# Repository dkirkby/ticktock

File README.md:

# Precision Pendulum Clock Metrology

This repository contains electronics schematics and a printed circuit board design for precision metrology of a pendulum clock.

The corresponding microcontroller firmware and unix server backend are hosted [here](https://github.com/captainkirkby/Gears).

For an overview of this project, see [this excerpt](https://github.com/dkirkby/ticktock/blob/master/InterfaceMagazineFall2015.pdf) from the Fall 2015 Issue of the [CalIT2](http://www.calit2.uci.edu) Interface Magazine.

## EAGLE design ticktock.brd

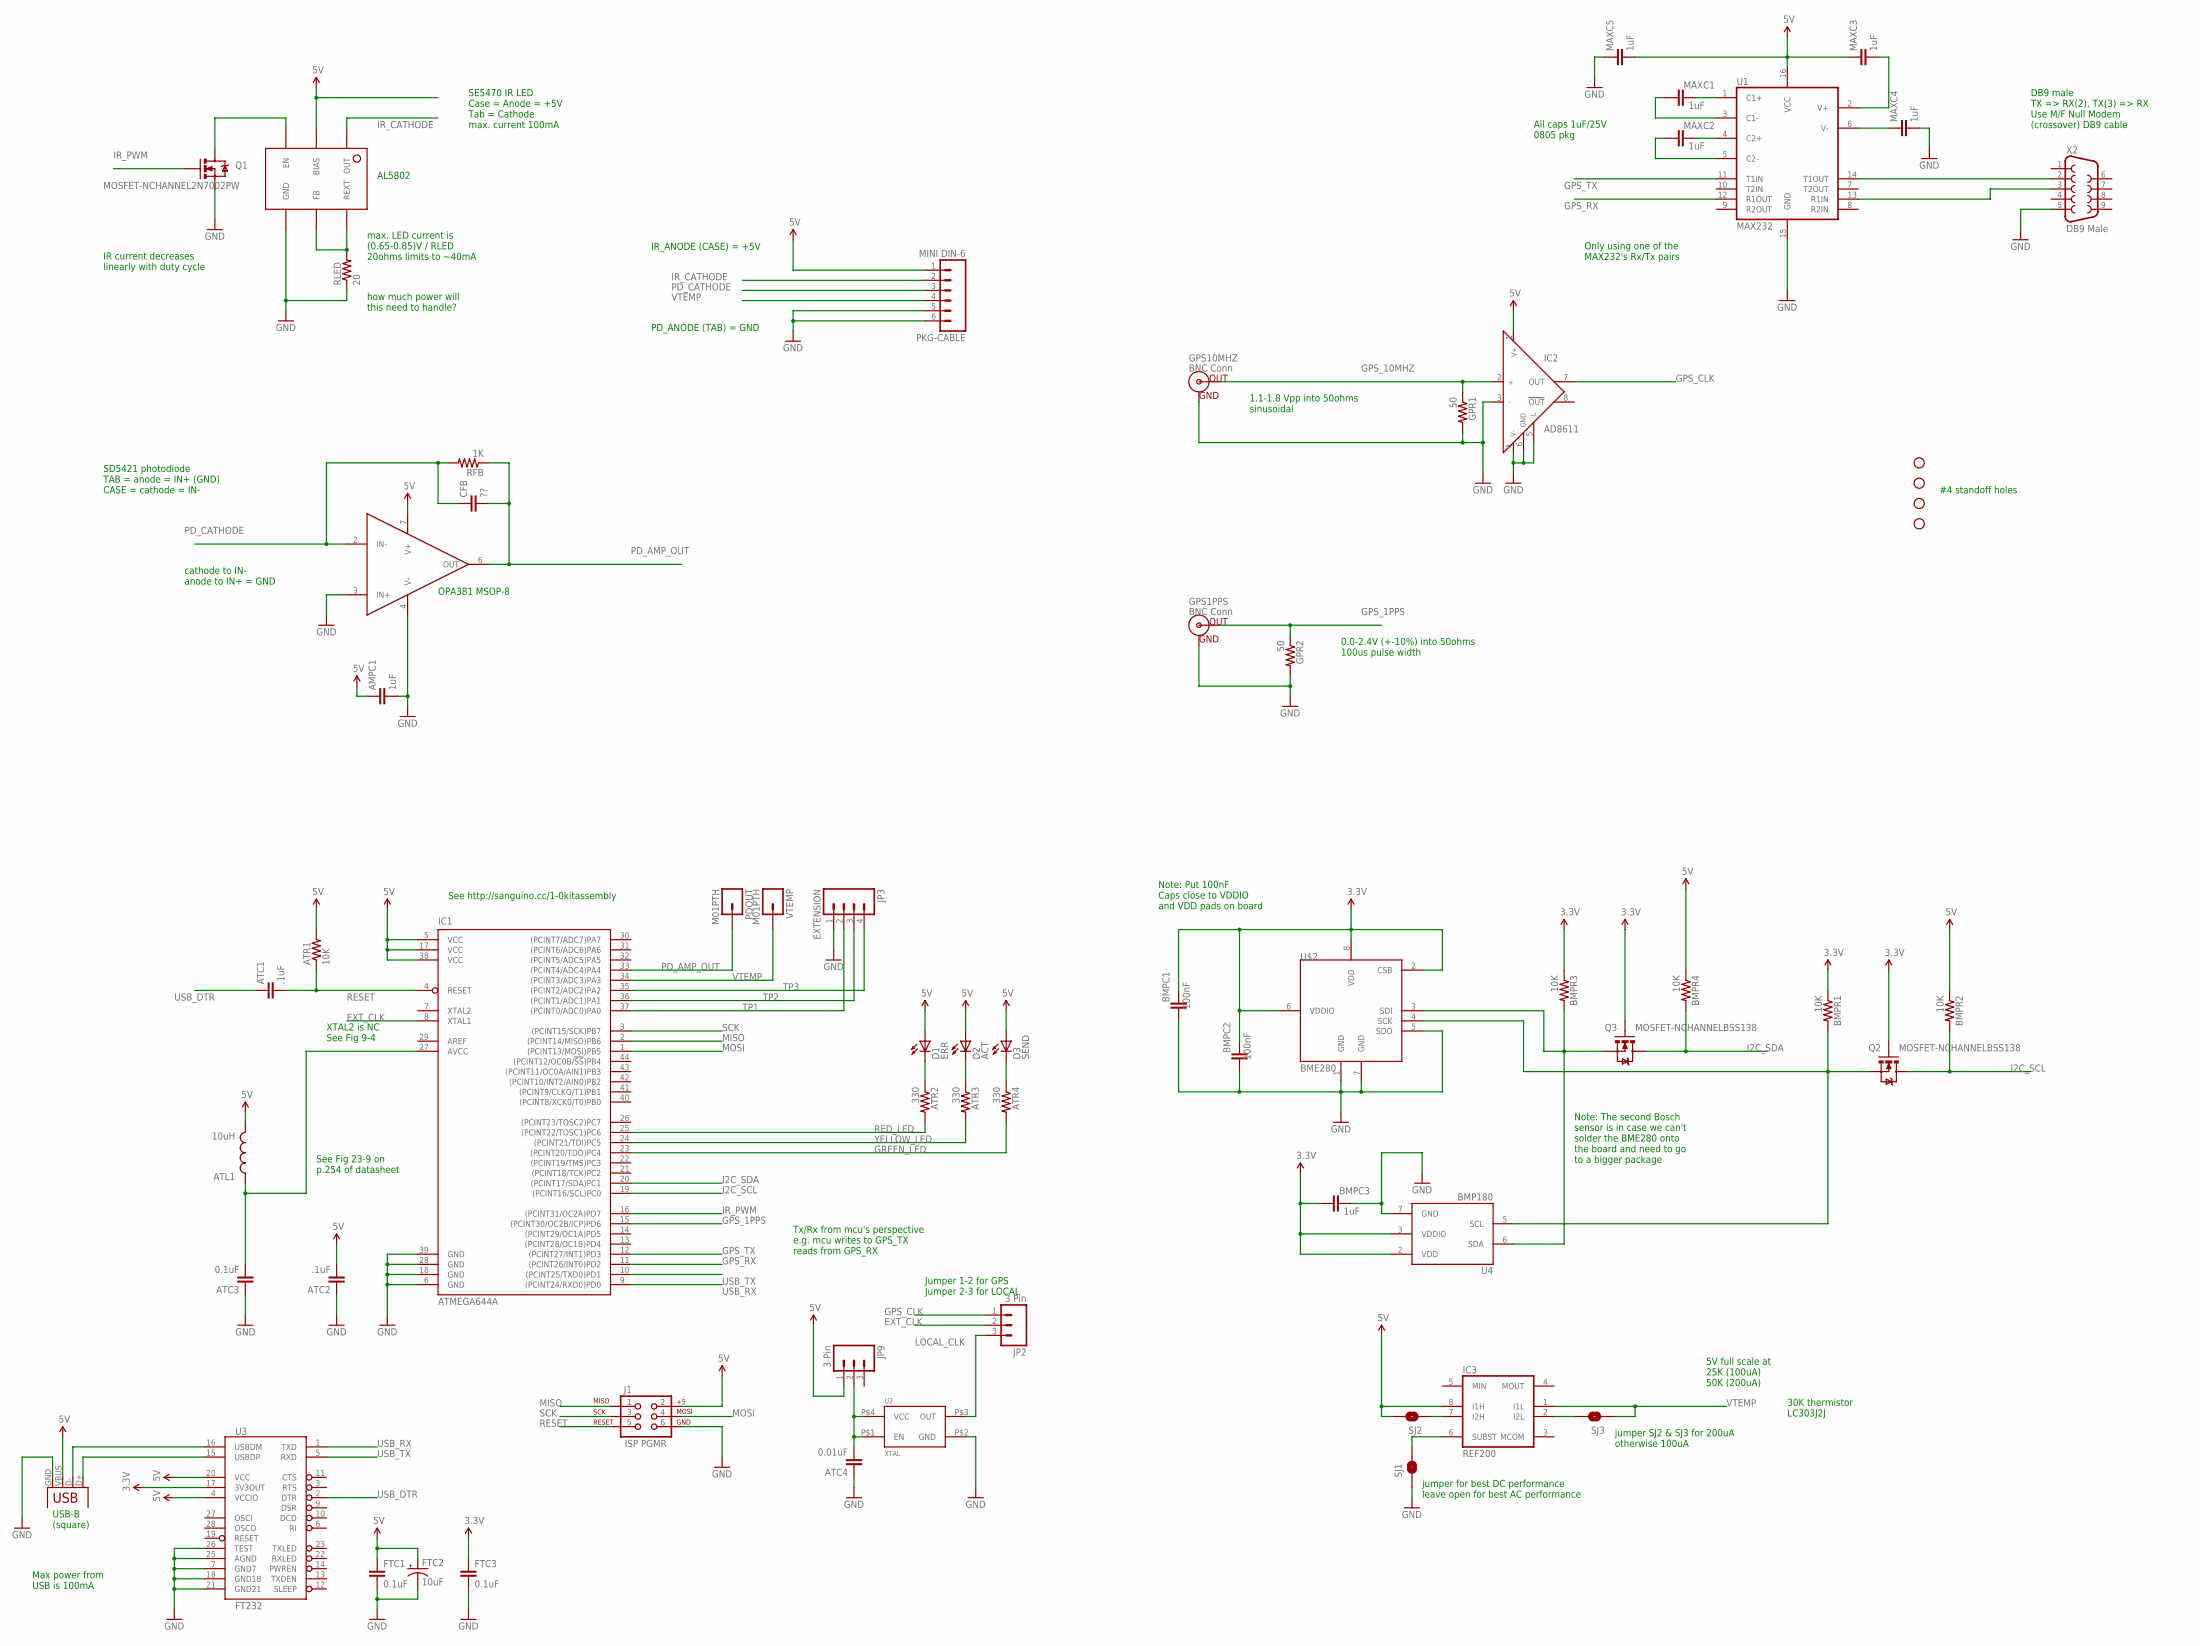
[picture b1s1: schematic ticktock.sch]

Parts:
AMPC1: 1uF; 0805
ATC1, ATC2: .1uF; 0805
ATC3: 0.1uF; 0805
ATC4: 0.01uF; 0805
ATL1: 10uH; 0805
ATR1: 10K; 0805
ATR2, ATR3, ATR4: 330; 0805
BMPC1, BMPC2: 100nF; 0805
BMPC3: 1uF; 0805
BMPR1, BMPR2, BMPR3, BMPR4: 10K; 0805
CFB: ??; 0805
D1: ERR; LED-1206
D2: ACT; LED-1206
D3: SEND; LED-1206
FTC1, FTC3: 0.1uF; 0805
FTC2: 10uF; EIA3216
GPR1, GPR2: 50; 0805
GPS1PPS, GPS10MHZ: BNC Conn; BNC
IC1: ATMEGA644A; TQFP44
IC2: AD8611; MSOP08
IC3: REF200; SO08
IC4: OPA381; MSOP08
IC5: AL5802
J1: ISP PGMR; 2X3-NS
JP1: Square USB; USB-B-PTH
JP2: 3 Pin; 1X03_LOCK
JP3: EXTENSION; 1X04_LOCK
JP9: 3-Pin; 1X03_LOCK
MAXC1, MAXC2, MAXC3, MAXC4, MAXC5: 1uF; 0805
PDOUT: M01PTH; 1X01
PKG-CABLE: MINI DIN-6; MINI-DIN6
Q1: MOSFET-NCHANNEL2N7002PW; SOT323
Q2, Q3: MOSFET-NCHANNELBSS138; SOT23
RFB: 1K; 0805
RLED: 20; 0805
SJ1, SJ2, SJ3: SOLDERJUMPERNO; SJ_2S-NO
STANDOFF1, STANDOFF2, STANDOFF3, STANDOFF4: STAND-OFF
U1: MAX232; SO016
U2: XTAL; CRYSTAL-SMD-7X5
U3: FT232; SSOP28DB
U4: BMP180
U$2: BME280
VTEMP: M01PTH; 1X01
X2: DB9 Male; DB9_MALE

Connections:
3.3V: BMPC1.2, BMPC2.2, BMPC3.1, BMPR1.1, BMPR3.1, FTC3.1, Q2.1 (G), Q3.1 (G), U3.17 (3V3OUT), U4.2 (VDD), U4.3 (VDDIO), U$2.2 (CSB), U$2.6 (VDDIO), U$2.8 (VDD)
5V: AMPC1.1, ATC2.2, ATL1.2, ATR1.2, BMPR2.1, BMPR4.1, D1.A, D2.A, D3.A, FTC1.1, FTC2.A (+), IC1.5 (VCC), IC1.17 (VCC), IC1.38 (VCC), IC2.1 (V+), IC3.8 (I1H), IC4.7 (V+), IC5.BIAS, J1.2, JP1.VBUS, JP9.1, MAXC3.1, MAXC5.2, PKG-CABLE.1, SJ2.2, U1.16 (VCC), U3.4 (VCCIO), U3.20 (VCC)
EXT_CLK: IC1.8 (XTAL1), JP2.2
GND: AMPC1.2, ATC2.1, ATC3.1, ATC4.1, BMPC1.1, BMPC2.1, BMPC3.2, FTC1.2, FTC2.C (-), FTC3.2, GPR1.2, GPR2.2, GPS1PPS.GND, GPS10MHZ.GND, IC1.6 (GND), IC1.18 (GND), IC1.28 (GND), IC1.39 (GND), IC2.3 (IN-), IC2.4 (V-), IC2.5 (L), IC2.6 (GND), IC4.3 (IN+), IC4.4 (V-), IC5.GND, J1.6, JP1.GND, JP3.1, MAXC4.2, MAXC5.1, PKG-CABLE.5, PKG-CABLE.6, Q1.2 (S), RLED.1, SJ1.1, U1.15 (GND), U2.P$2 (GND), U3.7 (GND7), U3.18 (GND18), U3.21 (GND21), U3.25 (AGND), U3.26 (TEST), U4.7 (GND), U$2.1 (GND), U$2.5 (SDO), U$2.7 (GND), X2.5
GPS_1PPS: GPR2.1, GPS1PPS.S (OUT), IC1.15 ((PCINT30/OC2B/ICP)PD6)
GPS_10MHZ: GPR1.1, GPS10MHZ.S (OUT), IC2.2 (IN+)
GPS_CLK: IC2.7 (OUT), JP2.1
GPS_RX: IC1.11 ((PCINT26/INT0)PD2), U1.12 (R1OUT)
GPS_TX: IC1.12 ((PCINT27/INT1)PD3), U1.11 (T1IN)
GREEN_LED: ATR4.2, IC1.23 ((PCINT20/TDO)PC4)
I2C_SCL: BMPR2.2, IC1.19 ((PCINT16/SCL)PC0), Q2.3 (D)
I2C_SDA: BMPR4.2, IC1.20 ((PCINT17/SDA)PC1), Q3.3 (D)
IR_CATHODE: IC5.OUT, PKG-CABLE.2
IR_PWM: IC1.16 ((PCINT31/OC2A)PD7), Q1.1 (G)
LOCAL_CLK: JP2.3, U2.P$3 (OUT)
MISO: IC1.2 ((PCINT14/MISO)PB6), J1.1
MOSI: IC1.1 ((PCINT13/MOSI)PB5), J1.4
unnamed: IC5.EN, Q1.3 (D)
unnamed: IC5.FB, IC5.REXT, RLED.2
unnamed: MAXC1.2, U1.1 (C1+)
unnamed: MAXC1.1, U1.3 (C1-)
unnamed: MAXC2.2, U1.4 (C2+)
unnamed: MAXC2.1, U1.5 (C2-)
unnamed: MAXC3.2, U1.2 (V+)
unnamed: U1.14 (T1OUT), X2.2
unnamed: MAXC4.1, U1.6 (V-)
unnamed: U1.13 (R1IN), X2.3
unnamed: JP1.D-, U3.16 (USBDM)
unnamed: JP1.D+, U3.15 (USBDP)
unnamed: ATC3.2, ATL1.1, IC1.27 (AVCC)
unnamed: IC3.6 (SUBST), SJ1.2
unnamed: BMPR1.2, Q2.2 (S), U4.5 (SCL), U$2.4 (SCK)
unnamed: ATR4.1, D3.C
unnamed: IC3.7 (I2H), SJ2.1
unnamed: IC3.2 (I2L), SJ3.2
unnamed: ATR3.1, D2.C
unnamed: ATR2.1, D1.C
unnamed: ATC4.2, JP9.2, U2.P$1 (EN), U2.P$4 (VCC)
unnamed: BMPR3.2, Q3.2 (S), U4.6 (SDA), U$2.3 (SDI)
PD_AMP_OUT: CFB.2, IC1.33 ((PCINT4/ADC4)PA4), IC4.6 (OUT), PDOUT.1, RFB.1
PD_CATHODE: CFB.1, IC4.2 (IN-), PKG-CABLE.3, RFB.2
RED_LED: ATR2.2, IC1.25 ((PCINT22/TOSC1)PC6)
RESET: ATC1.2, ATR1.1, IC1.4 (RESET), J1.5
SCK: IC1.3 ((PCINT15/SCK)PB7), J1.3
TP1: IC1.37 ((PCINT0/ADC0)PA0), JP3.2
TP2: IC1.36 ((PCINT1/ADC1)PA1), JP3.3
TP3: IC1.35 ((PCINT2/ADC2)PA2), JP3.4
USB_DTR: ATC1.1, U3.2 (DTR)
USB_RX: IC1.9 ((PCINT24/RXD0)PD0), U3.1 (TXD)
USB_TX: IC1.10 ((PCINT25/TXD0)PD1), U3.5 (RXD)
VTEMP: IC1.34 ((PCINT3/ADC3)PA3), IC3.1 (I1L), PKG-CABLE.4, SJ3.1, VTEMP.1
YELLOW_LED: ATR3.2, IC1.24 ((PCINT21/TDI)PC5)

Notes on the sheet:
max. LED current is (0.65-0.85)V / RLED 20ohms limits to ~40mA
SE5470 IR LED Case = Anode = +5V Tab = Cathode max. current 100mA
how much power will this need to handle?
IR current decreases linearly with duty cycle
AL5802
All caps 1uF/25V 0805 pkg
Only using one of the MAX232's Rx/Tx pairs
DB9 male TX => RX(2), TX(3) => RX Use M/F Null Modem (crossover) DB9 cable
USB-B (square)
Max power from USB is 100mA
See Fig 23-9 on p.254 of datasheet
IR_ANODE (CASE) = +5V
XTAL2 is NC See Fig 9-4
See http://sanguino.cc/1-0kitassembly
Jumper 1-2 for GPS Jumper 2-3 for LOCAL
0.0-2.4V (+-10%) into 50ohms 100us pulse width
1.1-1.8 Vpp into 50ohms sinusoidal
OPA381 MSOP-8
cathode to IN- anode to IN+ = GND
SD5421 photodiode TAB = anode = IN+ (GND) CASE = cathode = IN-
PD_ANODE (TAB) = GND
jumper for best DC performance leave open for best AC performance
jumper SJ2 & SJ3 for 200uA otherwise 100uA
5V full scale at 25K (100uA) 50K (200uA)
30K thermistor LC303J2J
#4 standoff holes
Note: Put 100nF Caps close to VDDIO and VDD pads on board
Note: The second Bosch sensor is in case we can't solder the BME280 onto the board and need to go to a bigger package
Tx/Rx from mcu's perspective e.g. mcu writes to GPS_TX reads from GPS_RX

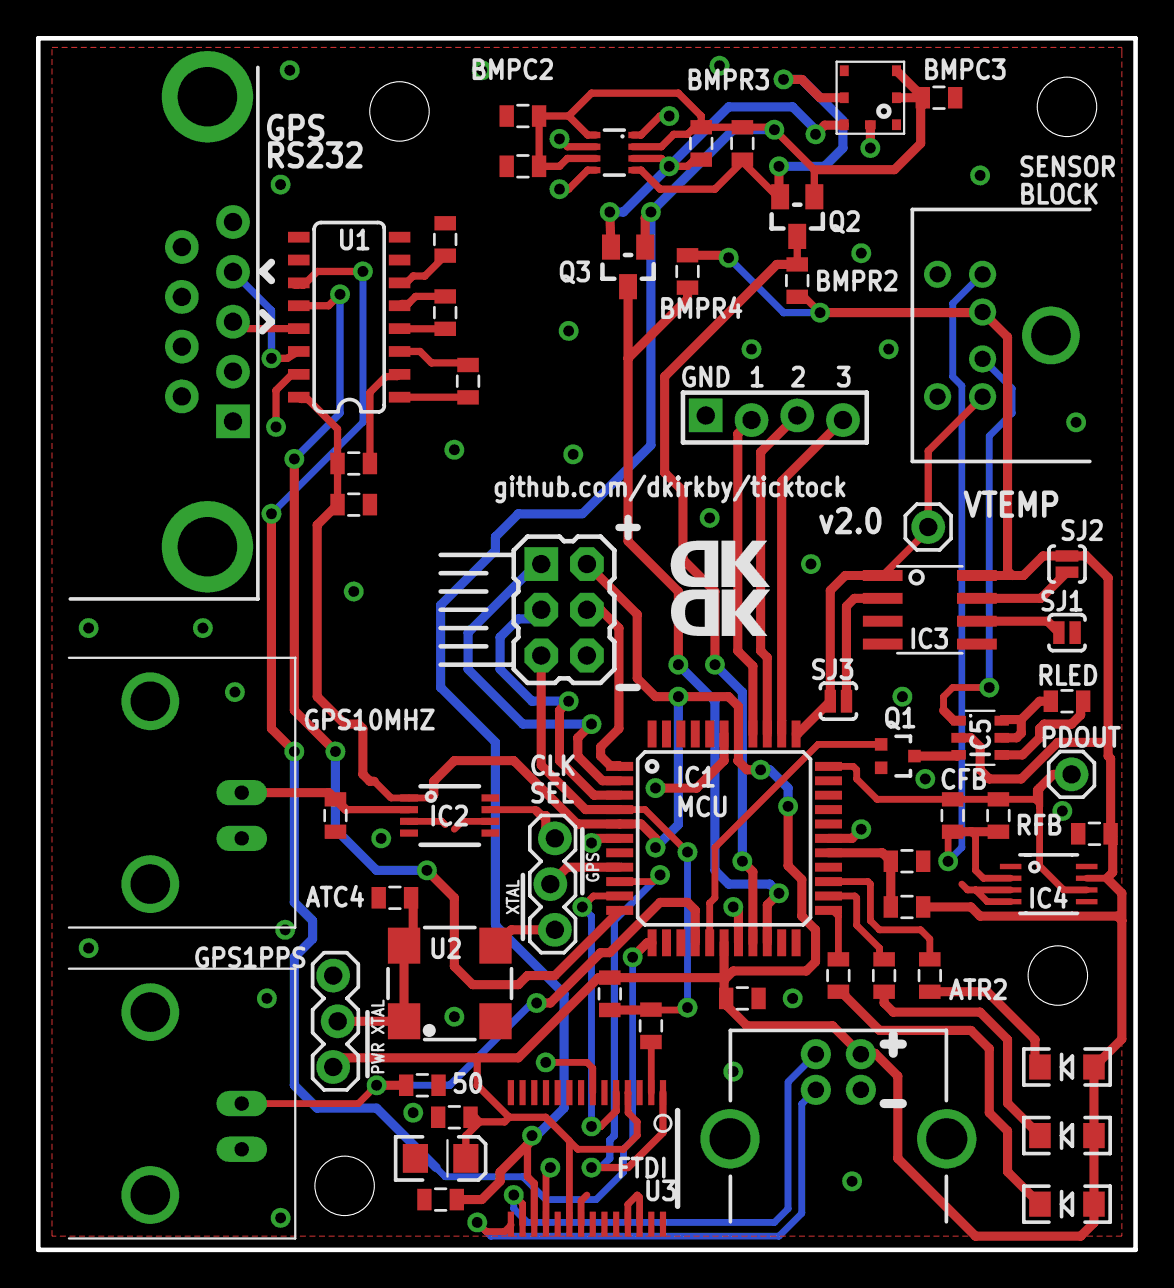
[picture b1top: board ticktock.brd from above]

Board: 2 copper layers, 61.0 x 67.3 mm, 64 parts (0 on the bottom side), 52 nets.

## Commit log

2013-12-06 initial commit of new (blanck) project created with Eagle 6.5.0
2013-12-06 Add schematic with 8.5x11 landscape frame
2013-12-06 Add 2x2 grid of schematic frames
2013-12-06 Add ignore file
2013-12-06 stop tracking eagle project file which is not portable
2013-12-06 Add power nodes from sparkfun git library
2013-12-07 add some components for the LED driver
2013-12-07 create initial board file
2013-12-17 Add empty component library.
2013-12-17 Create AL5802 Package.
2013-12-17 Create AL5802 Symbol
2013-12-18 Create AL5802 Device. Ready for use in Eagle now.
2013-12-18 Finish IR led current source
2013-12-18 add mini-DIN6 connector to package
2013-12-18 Add RS232 transceiver and DB9 connector
2013-12-18 Relabel MAX caps
2013-12-18 Add BNC connectors and AVR644
2013-12-18 Add FTDI USB interface
2013-12-18 Add MCU power and reset
2013-12-19 Add some MCU connections
2013-12-19 Add local 10MHz osc and local/gps jumper block
2013-12-19 Add comparator for GPS 10MHz
2013-12-19 Add 50ohm termination on 1PPS input
2013-12-19 Add op-amp schematic (missing actual op-amp)
2013-12-19 Add OPA381 Part to Library
2013-12-20 Finish op-amp circuit
2013-12-20 Add thermistor 100/200uA current source
2013-12-20 Add BMP180 and level shifters
2013-12-20 wire up analog inputs and I2C to MCU
2013-12-20 Add 3 indicator LEDs
2013-12-20 Add test points
2013-12-20 Add header for fallback BMP085 carrier board
2013-12-20 Group sensors on mini-DIN
2013-12-20 Recenter subcircuits in schematic
2013-12-20 Add thermistor info in a label
2013-12-20 First pass at board placement
2013-12-20 Fix USB connector label (A -> B)
2013-12-20 Add four 2.8mm PCB mounting holes
2013-12-21 Add 0.05" grid, make tDocu layer yellow
2013-12-21 Move connectors so their silkscreens fit on pcb
2013-12-21 Replace existing holes with SparkFun #4 standoff holes
2013-12-21 Add a bottom ground plane
2013-12-21 Remove ground plane for now since it only cleans up through hole ground connections
2013-12-21 Start placing around origin
2013-12-21 fix schematic broken connections
2013-12-21 Add power jumper for local 10MHz
2013-12-21 finish first pass at placement
2013-12-21 Trim board to 2.4 x 2.6 inches
2013-12-22 Relaid out Barometric Pressure Sensor part of board
2013-12-23 fine tune positions
2013-12-23 swap LEDs and resistors to get LEDs into PCB corner
2013-12-23 change grid from 0.05 to 0.01
2013-12-23 start routing
2013-12-23 more routing
2013-12-23 Route Barometric Pressure Sensor part of board.
2013-12-23 Route easy bits of MAX232 transceiver part of board.
2013-12-23 Route 5V power traces.
2013-12-23 Route 5V under chip.
2013-12-23 Preliminary Route completed.
2013-12-24 Fix traces around RS232 pins to use vias instead.
2013-12-24 Replace SO8 package of ultrafast comparator with MSOP8 package.
2013-12-24 Add power to pin 4 of FTDI chip.
2013-12-24 Fix ERC and DRC complaints. Connect accidentally unconnected nets.
2013-12-24 add bottom ground plane
2013-12-24 ease ground plane into a tight spot
2013-12-24 Add top ground plane
2013-12-24 hand route ground vias
2013-12-24 only 2 airwires left...
2013-12-24 finished routing!
2013-12-24 Fix up DRC clearance complaints.
2013-12-24 Modify board to conform to SparkFun's DRC file.
2013-12-24 Generate Gerber files for board.
2013-12-24 Modify board to generate gerber file without edge.
2013-12-24 Increse board dimension outline to 10 mil.
2013-12-24 Add sparkfun .cam file used to generate gerber files.
2015-06-20 Remove BMP carrier board header and Pull RS232 connector back to PCB edge
2015-06-20 Move 10uF cap closer to FTDI chip
2015-06-20 Replace DB9 female connector with a male one
2015-06-20 Flip USB_TX and USB_RX in schematic
2015-06-20 Flip USB_TX and USB_RX in board
2015-06-21 Add BME280 to Tick Tock Eagle Library
2015-06-21 Drop in BME280 (remove BMP180)
2015-06-21 Place new BME280 and old BMP180 on board
2015-06-25 Clean up DRC errors
2015-06-25 Modify Silkscreen of BME280
2015-06-25 Clean up ERC and add pin 1 marker on BME280
2015-06-25 Add silkscreen indicating RS232 polarity and ISP header direction
2015-06-25 Relabel USB_TX and USB_RX to be consistent with MCU's perspective
2015-06-25 Reroute right angle wire
2015-06-25 Add silkscreen for MAX232
2015-06-26 Start working on silkscreen
2015-06-26 Finish preliminary silkscreen
2015-06-26 More work on silkscreen
2015-06-26 Shuffle tight parts/silkscreens around
2015-06-26 Modify Silkscreen for AL5802
2015-06-26 Modify Silkscreen for OPA381
2015-06-26 Modify Silkscreen for FT232
2015-06-26 Modify Silkscreen for N-Channel MOSFET
2015-06-26 Modify AD8611 Silkscreen
2015-06-26 Add BNC keepaway
2015-06-26 Add 4 pin sensor extension header
2015-06-28 Add logo, url, and version number. Pour ground around BNC connectors
2015-06-28 Modify silkscreen of 4 pin header
2015-06-29 Modify Sparkfun .cam file to include tNAmes and tValues in silkscreen
2015-06-29 Move silkscreens of connectors away from the board edge
2015-06-29 Generate unpanelized gerber files for verification
2015-06-30 Fix FreeDFM.org complaints about skinny silkscreens
2015-07-01 Widen small silkscreen text
2015-07-01 Generate Gerber files
2015-07-01 Add gerbmerge config file for panelizing gerber files
2015-07-02 Confirm gerbmerge output visually with gerbv and programatically with FreeDFM. Ready to fab

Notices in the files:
parts and their libraries:
SparkFun-DiscreteSemi: Licensing: CC v3.0 Share-Alike You are welcome to use this library for commercial purposes.
